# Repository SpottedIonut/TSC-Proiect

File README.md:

#### Spirchez Mihai 331CA
## Block Diagram
```mermaid
graph TD
  %% Center
  ESP[<span style='color:#e0ccff'><b>ESP32</b></span>]

  %% SPI Devices (Top)
  NOR[<span style='color:#ffcccc'>External NOR Flash</span>]
  EPD[<span style='color:#ffcccc'>E-Paper Display</span>]
  SD[<span style='color:#ffcccc'>SD Card</span>]

  NOR -->|SPI| ESP
  ESP -->|SPI| EPD
  SD -->|SPI| ESP

  %% I2C Devices (Bottom)
  RTC[<span style='color:#cce5ff'>RTC Module</span>]
  ENV[<span style='color:#cce5ff'>Environmental Sensor</span>]
  BCL[<span style='color:#cce5ff'>Battery Charge Level</span>]

  RTC -->|I2C| ESP
  ENV -->|I2C| ESP
  BCL -->|I2C| ESP

  %% Buttons (Left)
  BTN[<span style='color:#d4f4dd'>Buttons</span>]
  BTN --> ESP

  %% USB and Power (Right)
  USB[USB C Connector]
  CHG[Charging Controller]
  REG[Voltage Regulator]
  BATT[Battery]

  ESP -->|USB| USB
  USB --> CHG
  USB --> REG
  BATT --> CHG
  BATT --> REG

```
## Bill of Materials
|Component|Description|Purchase|Datasheet|
|---------|-----------|--------|---------|
|EAGLE-LTSPICE_CC0402 | Capacitor | https://eu.mouser.com/ProductDetail/KEMET/C0402C475K8PACTU?qs=ulEaXIWI0c9ebKRT3r3htg%3D%3D | https://eu.mouser.com/datasheet/2/447/KEM_C1006_X5R_SMD-3316465.pdf
|ESP32_WROVER_EAGLE-LTSPICE_RR0402 | Resistor | https://eu.mouser.com/ProductDetail/Vishay-Beyschlag/MCS04020D9101BE000?qs=sGAEpiMZZMvdGkrng054twKDKoBh%252BscnK%2FuqkNk9X%252BqO%2Fz5%2F0u93Ow%3D%3D  | https://www.vishay.com/docs/28700/mcx0x0xpre.pdf
|RCL_CPOL-EUCT3528 | Capacitor | https://eu.mouser.com/ProductDetail/Nichicon/LGN2W101MELA25?qs=Fe64Qgzkstf1zMszMsgRoA%3D%3D | https://eu.mouser.com/datasheet/2/293/e_lgn-3082370.pdf
|ADAFRUIT_LEDCHIP-LED0603 | LED | https://eu.mouser.com/ProductDetail/ams-OSRAM/KG-EELP41.22-PHRH-35-A8J8-20-R18?qs=ZcfC38r4Posajg8ZvCDQkg%3D%3D | https://eu.mouser.com/datasheet/2/588/KG_EELP41_22_EN-3572852.pdf
|CPH3225A | Capacitor | https://eu.mouser.com/ProductDetail/Seiko-Semiconductors/CPH3225A?qs=3etwrb1wR%252BhUOph6lAO7eg%3D%3D | https://eu.mouser.com/datasheet/2/360/Seiko_Instruments_MicroBattery_E_20230330_2024Jan_-3561061.pdf
|ESP32_WROVER_SPARKFUN-DISCRETESEMI_MOSFET_PCH-DMG2305UX-7 | Transistor | https://eu.mouser.com/ProductDetail/Diodes-Incorporated/DMG2305UX-7?qs=L1DZKBg7t5F%2FNBHrjfxC%252Bg%3D%3D | https://www.diodes.com/assets/Datasheets/DMG2305UX.pdf
|ESP32_WROVER_AVX---SD0805S020S1R0_AVX_SD0805S020S1R0_0_0AVX_SD0805S020S1R0_0_0 | Diode | https://eu.mouser.com/ProductDetail/ROHM-Semiconductor/SCS310AMC7G?qs=iLKYxzqNS75xiccEgNnX2g%3D%3D | https://fscdn.rohm.com/en/products/databook/datasheet/discrete/sic/sbd/scs310am-e.pdf
|SI1308EDL-T1-GE3 | Transistor | https://eu.mouser.com/ProductDetail/Vishay-Semiconductors/SI1308EDL-T1-GE3?qs=bX1%252BNvsK%2FBramh9tgpOaEw%3D%3D | https://www.vishay.com/docs/63399/si1308edl.pdf
|ESP32C6_VARISTORCN1812 | Varistor | https://eu.mouser.com/ProductDetail/Schurter/PFMF.050.2?qs=1auRipcfynCums5v1iucSA%3D%3D | https://eu.mouser.com/datasheet/2/358/typ_PFMF-1275918.pdf
|ESP32_WROVER_BME680_BME680 | Integrated Environmental Unit | https://eu.mouser.com/ProductDetail/M5Stack/U001-C?qs=e8oIoAS2J1R2mB7ZY1%252BSZg%3D%3D | https://docs.m5stack.com/en/unit/envIII
|ESP32-C6-WROOM-1-N8 | MicroController | https://eu.mouser.com/ProductDetail/Espressif-Systems/ESP32-C6?qs=Imq1NPwxi75noDtUpuVuWw%3D%3D | https://eu.mouser.com/datasheet/2/891/esp32_c6_datasheet_en-3304070.pdf
| 744043680IND_4828-WE-TPC_WRE | Inductor | https://eu.mouser.com/ProductDetail/Wurth-Elektronik/744043680?qs=PGXP4M47uW6VkZq%252BkzjrHA%3D%3D | https://www.we-online.com/components/products/datasheet/744043680.pdf
|SI1308EDL-T1-GE3 | Transistor | https://eu.mouser.com/ProductDetail/Vishay-Semiconductors/SI1308EDL-T1-GE3?qs=bX1%252BNvsK%2FBramh9tgpOaEw%3D%3D | https://www.vishay.com/docs/63399/si1308edl.pdf
| BD5229G-TR | Voltage Detector | https://eu.mouser.com/ProductDetail/ROHM-Semiconductor/BD5229G-TR?qs=sGAEpiMZZMutXGli8Ay4kAMqIQqqdOUlDFcDfPDPIK4%3D | https://fscdn.rohm.com/en/products/databook/datasheet/ic/power/voltage_detector/bd52xxg-e.pdf
|DS3231SN# | RTC Module | https://eu.mouser.com/ProductDetail/Analog-Devices-Maxim-Integrated/DS3231SN?qs=1eQvB6Dk1vhUlr8%2FOrV0Fw%3D%3D | https://eu.mouser.com/datasheet/2/609/DS3231-3421123.pdf
|USBLC6-2SC6Y | ESD Protection | https://eu.mouser.com/ProductDetail/STMicroelectronics/USBLC6-2SC6Y?qs=gNDSiZmRJS%2FOgDexvXkdow%3D%3D | https://eu.mouser.com/datasheet/2/389/usblc6_2sc6y-1852505.pdf
|W25Q512JVEIQ | Flash Memory | https://eu.mouser.com/ProductDetail/Winbond/W25Q512JVEIQ?qs=l7cgNqFNU1jw6svr3at6tA%3D%3D | https://eu.mouser.com/datasheet/2/949/Winbond_W25Q512JV_Datasheet-3240039.pdf
|SAMACSYS_PARTS_USB4110-GF-A | USB Connector | https://eu.mouser.com/ProductDetail/GCT/USB4110-GF-A?qs=KUoIvG%2F9IlYiZvIXQjyJeA%3D%3D | https://eu.mouser.com/datasheet/2/837/GCT_USB4110_Product_Drawing___20k_cycles-3455479.pdf
|FH34SRJ | E-Paper Display Header | https://eu.mouser.com/ProductDetail/Hirose-Connector/FH34SRJ-7S-0.5SH50?qs=vcbW%252B4%252BSTIqHa4IamMh36g%3D%3D | https://eu.mouser.com/datasheet/2/185/FH34SRJ_7S_0_5SH_50__CL0580_1200_0_50_2DDrawing_00-1615127.pdf
|MAX17048G+T10 | Battery Management | https://eu.mouser.com/ProductDetail/Analog-Devices-Maxim-Integrated/MAX17048G%2bT10?qs=D7PJwyCwLAoGnnn8jEPRBQ%3D%3D | https://eu.mouser.com/datasheet/2/609/MAX17048_MAX17049-3469099.pdf
|MCP73831 | Battery Controller | https://eu.mouser.com/ProductDetail/Microchip-Technology/MCP73831T-2ATI-MC?qs=yUQqVecv4qs9k7ug0bEXiw%3D%3D | https://eu.mouser.com/datasheet/2/268/MCP73831_Family_Data_Sheet_DS20001984H-3441711.pdf
|112A-TAAR-R03_ATTEND | SD Card Mount | https://store.comet.srl.ro/Catalogue/Product/43497/ | https://store.comet.srl.ro/Catalogue/Product/43497/
|XC6220A331MR-G | LDO Voltage Regulator | https://eu.mouser.com/ProductDetail/Torex-Semiconductor/XC6220A331MR-G?qs=AsjdqWjXhJ8ZSWznL1J0gg%3D%3D | https://eu.mouser.com/datasheet/2/760/xc6220-3371556.pdf

## Hardware components
- ESP32-C6-WROOM-1-N8 Microcontroller

### Communication interfaces

| Communication interface | Connected Components |
|--------------|----------------------|
| I2C        | RTC, BME688, Battery Level     |
| SPI        | SD Card, E-Paper Display, NOR Flash     |
| USB        | USB C Connector / Power     |

### ESP32-C6-WROOM-1-N8 Pin Mapping

| ESP32 Pin | Signal | Purpose |
|--------------|----------------------|---------|
| IO0        | INT_RTC     | RTC communication |
| IO1        | 32KHZ     | RTC communication |
| IO2        | MISO     | SD Card, NOR Flash |
| IO3        | EPD_BUSY     | EPD status |
| IO4        | SS_SD | SD Card |
| IO5        | EPD_DC | EPD Data/Command |
| IO6        | SCK  | BME688, SD Card, NOR Flash |
| IO7        | MOSI   | SD Card, NOR Flash, EPD |
| IO8        | GPIO8 | SD card select |
| IO9        | IO/BOOT   | Boot button |
| IO10       | EPD_CS   | EPD chip select|
| IO11       | FLASH_CS    | NOR Flash chip select |
| IO12       | USB_D-| USB communication |
| IO13       | USB_D+        | USB communication |
| IO15       | IO/CHANGE   | Button change |
| IO16       | TX   | Transmit |
| IO17       | RX   | Receive |
| IO18       | RTC_RST   | RTC reset |
| IO19       | I2C_PW   | BME688 power management |
| IO20       | EPD_3V3_C   | EPD |
| IO21       | SDA   | RTC, BME688, Battery Level (I2C data) |
| IO22       | SCL   | RTC, BME688, Battery Level (I2C clock) |
| IO23       | EPD_RST   | EPD reset |

- Real-Time Clock Module (RTC)
  - A DS3231SN RTC module
  - It communicates through I2C with the microcontroller
  - Pin connections:
      - SCL -> IO22
      - SDA -> IO21
      - RTC_RST -> IO18
      - 32KHZ -> IO1
      - INT_RTC -> IO0
- SD Card
  - It communicates through SPI
  - Pin connections:
    - MISO - IO2
    - SCK - IO6
    - MOSI - IO7
    - SS_SD - IO4
- E-Paper Display (EPD)
  - It communicates through SPI
  - Pin connections:
    - EPD_CS -> IO10
    - EPD_DC -> IO5
    - EPD_RST -> IO23
    - EPD_BUSY -> IO3
    - MOSI, SCK -> shared with SD
- Environmental Sensor
  - BME688 sensor
  - It communicates through I2C
  - Pin connections:
      - SCL -> IO22
      - SDA -> IO21
- Li-Po Battery Charging Controller
  - Battery Charge Level
    - It communicates through I2C
    - Pin connections:
        - SCL -> IO22
        - SDA -> IO21
- LDO Voltage Regulator
  - Lowers the 5V to 3.3V for the microcontroller and the attached modules
- SPI ESD Protection Lines
- NOR Flash 64MB
  - It communicates through SPI
  - Pin connections:
    - FLASH_CS -> IO11
    - SCK, MOSI, MISO
- USB
  - USB_D- -> IO12
  - USB_D+ -> IO13
- Buttons for user input
  - RESET -> EN
  - IO/BOOT -> IO9
  - IO/CHANGE -> IO15
- Qwiic / Stemma QT Connector
  - It communicates through I2C
  - SCL, SDA

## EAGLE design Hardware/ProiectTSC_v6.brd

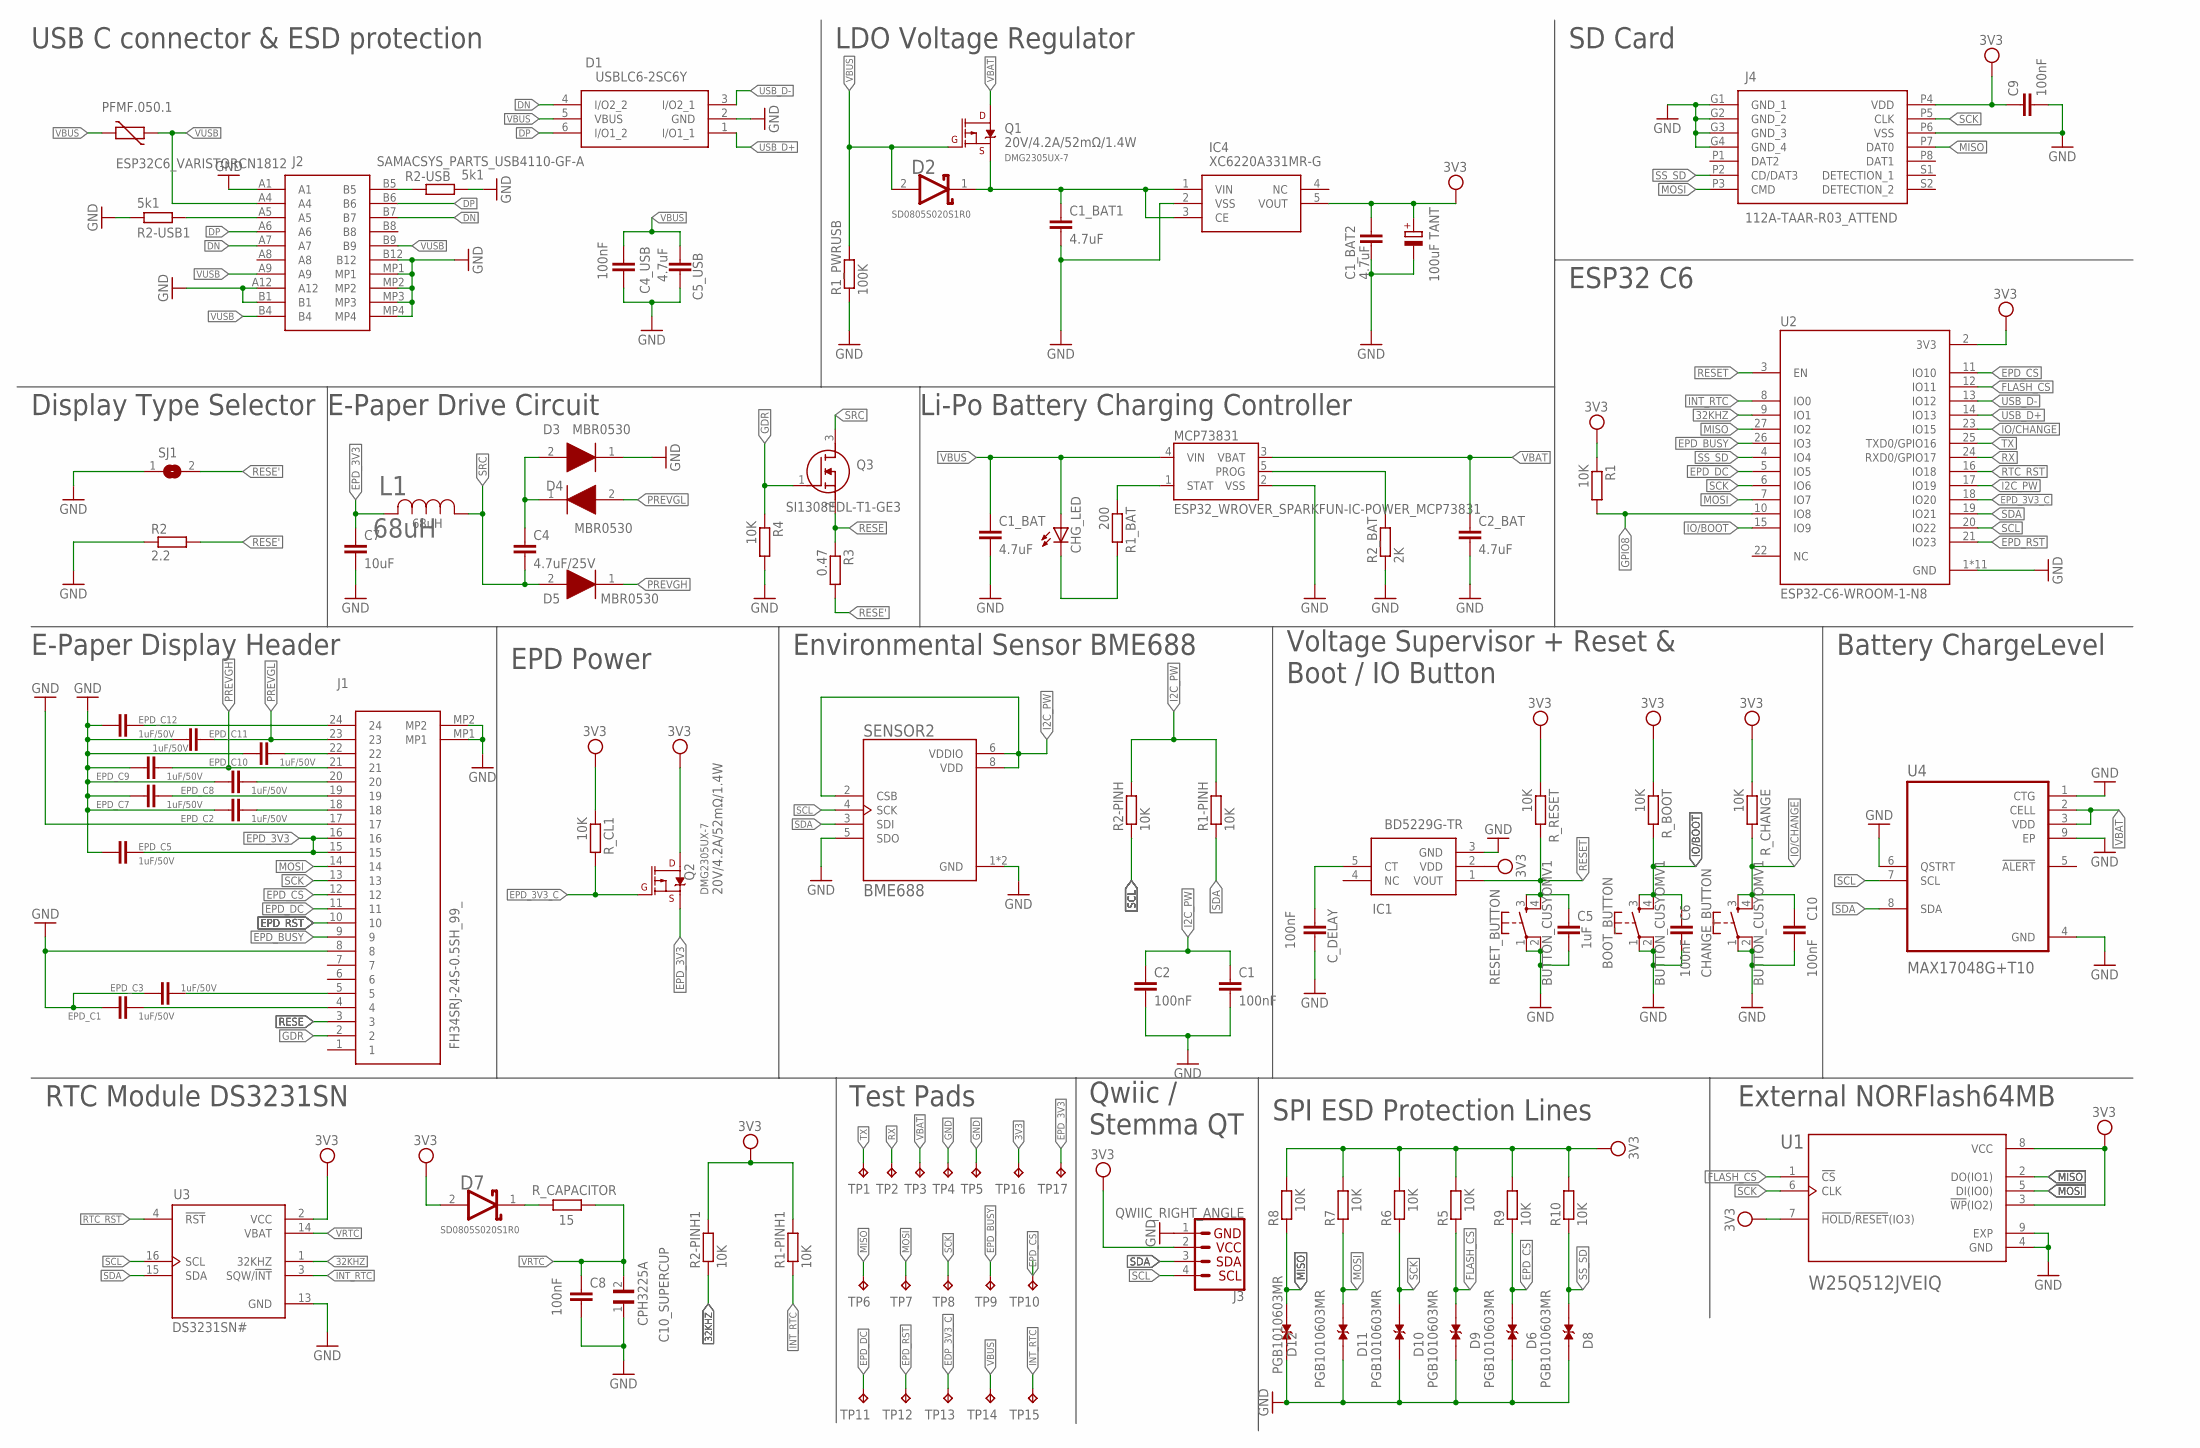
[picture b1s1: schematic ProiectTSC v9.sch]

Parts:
BOOT_BUTTON: BUTTON_CUSYOMV1; MYBUTTON
C1, C2, C4_USB, C6, C8, C9, C10: 100nF; EAGLE-LTSPICE_C0402
C1_BAT, C1_BAT1, C1_BAT2, C2_BAT, C5_USB: 4.7uF; EAGLE-LTSPICE_C0402
C4: 4.7uF/25V; EAGLE-LTSPICE_C0402
C5: 1uF; EAGLE-LTSPICE_C0402
C7: 10uF; EAGLE-LTSPICE_C0402
C10_SUPERCUP: CPH3225A; CAPCP3225X100N
CHANGE_BUTTON: BUTTON_CUSYOMV1; MYBUTTON
CHG_LED: ADAFRUIT_LEDCHIP-LED0603; ADAFRUIT_CHIP-LED0603
C_DELAY: 100nF; EAGLE-LTSPICE_C0402
D1: USBLC6-2SC6Y; SOT95P280X145-6N
D2, D7: SD0805S020S1R0; ESP32_WROVER_AVX---SD0805S020S1R0_AVX_SD0805S020S1R0_0
D3, D4, D5: MBR0530; SOD3716X135N
D6, D8, D9, D10, D11, D12: PGB1010603MR; DIOC1608X36N
EPD_C1, EPD_C2, EPD_C3, EPD_C5, EPD_C7, EPD_C8, EPD_C9, EPD_C10, EPD_C11, EPD_C12: 1uF/50V; EAGLE-LTSPICE_C0402
IC1: BD5229G-TR; SOT95P280X125-5N
IC4: XC6220A331MR-G; SOT95P280X120-5N
J1: FH34SRJ-24S-0.5SH_99_; FH34SRJ24S05SH99
J2: SAMACSYS_PARTS_USB4110-GF-A; SAMACSYS_PARTS_USB4110GFA
J3: QWIIC_RIGHT_ANGLE; JST04_1MM_RA
J4: 112A-TAAR-R03_ATTEND; 112ATAARR03ATTEND
L1: 68uH; IND_4828-WE-TPC_WRE
MCP73831: ESP32_WROVER_SPARKFUN-IC-POWER_MCP73831; ESP32_WROVER_SPARKFUN-IC-POWER_SOT23-5
PFMF.050.1: ESP32C6_VARISTORCN1812; ESP32C6_VARISTOR_CT/CN1812
Q1, Q2: 20V/4.2A/52mΩ/1.4W; ESP32_WROVER_SPARKFUN-DISCRETESEMI_SOT23-3
Q3: SI1308EDL-T1-GE3; SOT65P210X110-3N
R1, R1-PINH, R1-PINH1, R2-PINH, R2-PINH1, R4, R5, R6, R7, R8, R9, R10: 10K; ESP32_WROVER_EAGLE-LTSPICE_R0402
R1_BAT: 200; ESP32_WROVER_EAGLE-LTSPICE_R0402
R1_PWRUSB: 100K; ESP32_WROVER_EAGLE-LTSPICE_R0402
R2: 2.2; ESP32_WROVER_EAGLE-LTSPICE_R0402
R2-USB, R2-USB1: 5k1; ESP32_WROVER_EAGLE-LTSPICE_R0402
R2_BAT: 2K; ESP32_WROVER_EAGLE-LTSPICE_R0402
R3: 0.47; ESP32_WROVER_EAGLE-LTSPICE_R0402
RESET_BUTTON: BUTTON_CUSYOMV1; MYBUTTON
R_BOOT: 10K; ESP32_WROVER_EAGLE-LTSPICE_R0402
R_CAPACITOR: 15; ESP32_WROVER_EAGLE-LTSPICE_R0402
R_CHANGE: 10K; ESP32_WROVER_EAGLE-LTSPICE_R0402
R_CL1: 10K; ESP32_WROVER_EAGLE-LTSPICE_R0402
R_RESET: 10K; ESP32_WROVER_EAGLE-LTSPICE_R0402
SENSOR2: BME688; ESP32_WROVER_BME680_PSON80P300X300X100-8N
SJ1: SJ
TANT: 100uF; RCL_CT3528
TP1, TP2, TP3, TP4, TP5, TP6, TP7, TP8, TP9, TP10, TP11, TP12, TP13, TP14, TP15, TP16, TP17: TPTP20R; TP20R
U1: W25Q512JVEIQ; SON127P600X800X80-9N
U2: ESP32-C6-WROOM-1-N8; XCVR_ESP32-C6-WROOM-1-N8
U3: DS3231SN#; SOIC127P1032X265-16N
U4: MAX17048G+T10; SON50P200X200X80-9N

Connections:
3V3: C1_BAT2.1, C9.1, D7.2 (ANODE), IC1.2 (VDD), IC4.5 (VOUT), J3.2, J4.P4 (VDD), Q2.3 (D), R1.1, R1-PINH1.2, R2-PINH1.2, R5.2, R6.2, R7.2, R8.2, R9.2, R10.2, R_BOOT.1, R_CHANGE.1, R_CL1.1, R_RESET.1, TANT.+, TP16.TP, U1.3 (!WP!(IO2)), U1.7 (!HOLD!/!RESET!(IO3)), U1.8 (VCC), U2.2 (3V3), U3.2 (VCC)
32KHZ: R2-PINH1.1, U2.9 (IO1), U3.1 (32KHZ)
DN: D1.4 (I/O2_2), J2.A7, J2.B7
DP: D1.6 (I/O1_2), J2.A6, J2.B6
EDP_3V3_C: TP13.TP
EPD_3V3: C7.1, EPD_C5.1, J1.15, J1.16, L1.2, Q2.2 (S), TP17.TP
EPD_3V3_C: Q2.1 (G), R_CL1.2, U2.18 (IO20)
EPD_BUSY: J1.9, TP9.TP, U2.26 (IO3)
EPD_CS: D6.1, J1.12, R9.1, TP10.TP, U2.11 (IO10)
EPD_DC: J1.11, TP11.TP, U2.5 (IO5)
EPD_RST: J1.10, TP12.TP, U2.21 (IO23)
FLASH_CS: D9.1, R5.1, U1.1 (!CS), U2.12 (IO11)
GDR: J1.2, Q3.1 (G), R4.1
GND: BOOT_BUTTON.1, BOOT_BUTTON.2, C1.2, C1_BAT.2, C1_BAT1.2, C1_BAT2.2, C2.2, C2_BAT.2, C4_USB.2, C5.2, C5_USB.2, C6.2, C7.2, C8.2, C9.2, C10.2, C10_SUPERCUP.1, CHANGE_BUTTON.1, CHANGE_BUTTON.2, C_DELAY.2, D1.2 (GND), D3.1 (K), D6.2, D8.2, D9.2, D10.2, D11.2, D12.2, EPD_C1.2, EPD_C2.2, EPD_C3.2, EPD_C5.2, EPD_C7.2, EPD_C8.2, EPD_C9.2, EPD_C10.2, EPD_C11.2, EPD_C12.2, IC1.3 (GND), IC4.2 (VSS), J1.8, J1.17, J1.MP1, J1.MP2, J2.A1, J2.A12, J2.B1, J2.B12, J2.MP1, J2.MP2, J2.MP3, J2.MP4, J3.1, J4.G1 (GND_1), J4.G2 (GND_2), J4.G3 (GND_3), J4.G4 (GND_4), J4.P6 (VSS), MCP73831.2 (VSS), R1_PWRUSB.1, R2.1, R2-USB.2, R2-USB1.1, R2_BAT.1, R4.2, RESET_BUTTON.1, RESET_BUTTON.2, SENSOR2.1 (GND), SENSOR2.5 (SDO), SENSOR2.7 (GND), SJ1.1, TANT.-, TP4.TP, TP5.TP, U1.4 (GND), U1.9 (EXP), U2.1 (GND), U2.28 (GND), U2.29_1 (GND), U2.29_2 (GND), U2.29_3 (GND), U2.29_4 (GND), U2.29_5 (GND), U2.29_6 (GND), U2.29_7 (GND), U2.29_8 (GND), U2.29_9 (GND), U3.13 (GND), U4.1 (CTG), U4.4 (GND), U4.6 (QSTRT), U4.9 (EP)
GPIO8: R1.2, U2.10 (IO8)
I2C_PW: C1.1, C2.1, R1-PINH.2, R2-PINH.2, SENSOR2.2 (CSB), SENSOR2.6 (VDDIO), SENSOR2.8 (VDD), U2.17 (IO19)
INT_RTC: R1-PINH1.1, TP15.TP, U2.8 (IO0), U3.3 (SQW/!INT)
IO/BOOT: BOOT_BUTTON.3, BOOT_BUTTON.4, C6.1, R_BOOT.2, U2.15 (IO9)
IO/CHANGE: C10.1, CHANGE_BUTTON.3, CHANGE_BUTTON.4, R_CHANGE.2, U2.23 (IO15)
MISO: D12.1, J4.P7 (DAT0), R8.1, TP6.TP, U1.2 (DO(IO1)), U2.27 (IO2)
MOSI: D11.1, J1.14, J4.P3 (CMD), R7.1, TP7.TP, U1.5 (DI(IO0)), U2.7 (IO7)
unnamed: MCP73831.5 (PROG), R2_BAT.2
unnamed: J2.A5, R2-USB1.2
unnamed: MCP73831.1 (STAT), R1_BAT.1
unnamed: C4.1, D3.2 (A), D4.1 (K)
unnamed: C1_BAT1.1, D2.1 (CATHODE), IC4.1 (VIN), IC4.3 (CE), Q1.2 (S)
unnamed: CHG_LED.C, R1_BAT.2
unnamed: EPD_C12.1, J1.24
unnamed: J2.B5, R2-USB.1
unnamed: EPD_C10.1, J1.22
unnamed: C_DELAY.1, IC1.5 (CT)
unnamed: D7.1 (CATHODE), R_CAPACITOR.2
unnamed: EPD_C8.1, J1.20
unnamed: EPD_C7.1, J1.19
unnamed: EPD_C2.1, J1.18
unnamed: EPD_C1.1, J1.4
unnamed: EPD_C3.1, J1.5
PREVGH: D5.1 (K), EPD_C9.1, J1.21
PREVGL: D4.2 (A), EPD_C11.1, J1.23
RESE: J1.3, Q3.2 (S), R3.1
RESE': R2.2, R3.2, SJ1.2
RESET: C5.1, IC1.1 (VOUT), RESET_BUTTON.3, RESET_BUTTON.4, R_RESET.2, U2.3 (EN)
RTC_RST: U2.16 (IO18), U3.4 (!RST)
RX: TP2.TP, U2.24 (RXD0/GPIO17)
SCK: D10.1, J1.13, J4.P5 (CLK), R6.1, TP8.TP, U1.6 (CLK), U2.6 (IO6)
SCL: J3.4, R2-PINH.1, SENSOR2.4 (SCK), U2.20 (IO22), U3.16 (SCL), U4.7 (SCL)
SDA: J3.3, R1-PINH.1, SENSOR2.3 (SDI), U2.19 (IO21), U3.15 (SDA), U4.8 (SDA)
SRC: C4.2, D5.2 (A), L1.1, Q3.3 (D)
SS_SD: D8.1, J4.P2 (CD/DAT3), R10.1, U2.4 (IO4)
TX: TP1.TP, U2.25 (TXD0/GPIO16)
USB_D+: D1.1 (I/O1_1), U2.14 (IO13)
USB_D-: D1.3 (I/O2_1), U2.13 (IO12)
VBAT: C2_BAT.1, MCP73831.3 (VBAT), Q1.3 (D), TP3.TP, U4.2 (CELL), U4.3 (VDD)
VBUS: C1_BAT.1, C4_USB.1, C5_USB.1, CHG_LED.A, D1.5 (VBUS), D2.2 (ANODE), MCP73831.4 (VIN), PFMF.050.1.2, Q1.1 (G), R1_PWRUSB.2, TP14.TP
VRTC: C8.1, C10_SUPERCUP.2, R_CAPACITOR.1, U3.14 (VBAT)
VUSB: J2.A4, J2.A9, J2.B4, J2.B9, PFMF.050.1.1

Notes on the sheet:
USB C connector & ESD protection
LDO Voltage Regulator
SD Card
ESP32 C6
Display Type Selector
E-Paper Drive Circuit
Li-Po Battery Charging Controller
E-Paper Display Header
EPD Power
Environmental Sensor BME688
Voltage Supervisor + Reset & Boot / IO Button
Battery ChargeLevel
External NORFlash64MB
SPI ESD Protection Lines
Qwiic / Stemma QT
Test Pads
RTC Module DS3231SN

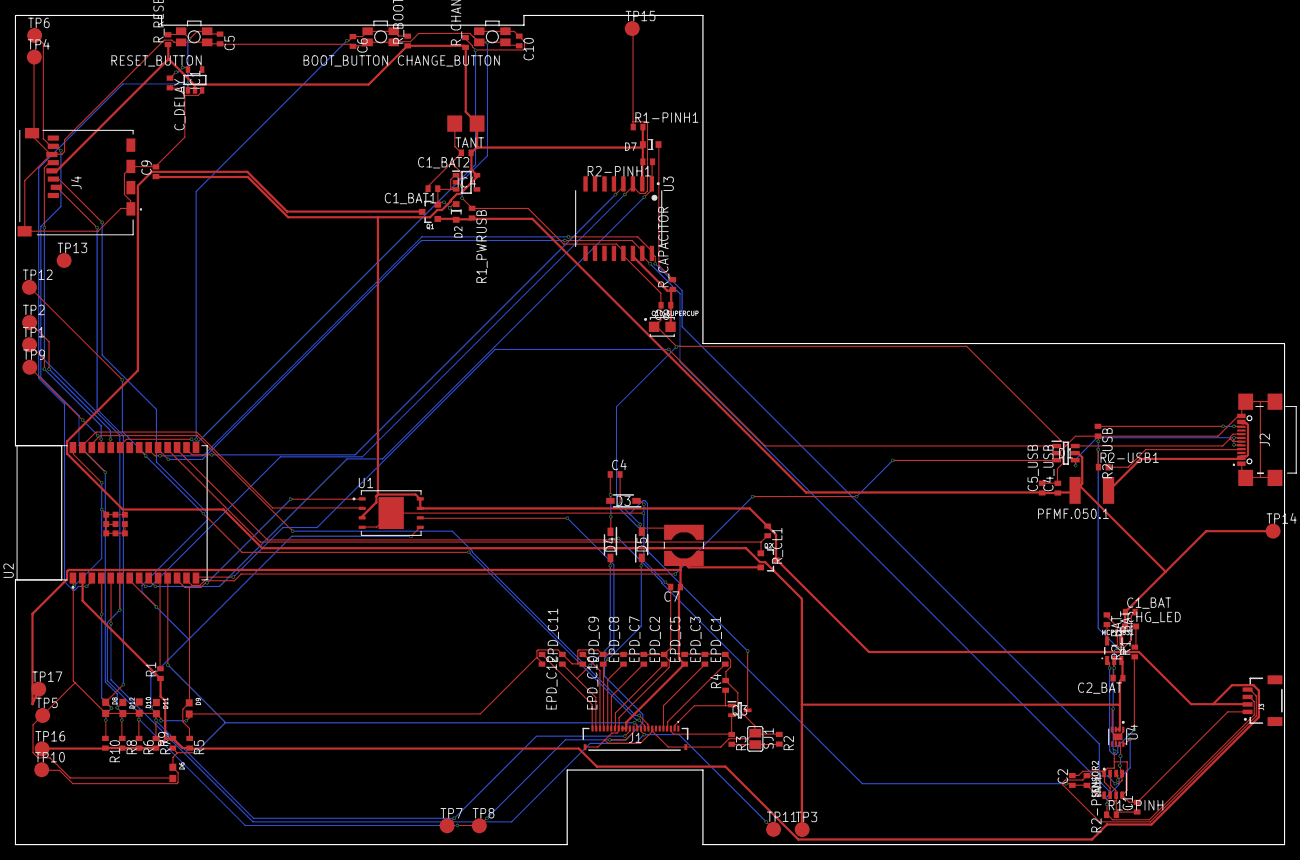
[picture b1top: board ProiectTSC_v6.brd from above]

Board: 2 copper layers, 170.2 x 111.2 mm, 103 parts (0 on the bottom side), 55 nets.

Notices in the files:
parts and their libraries:
DeskAssistant v19 v1: COPYRIGHT: Copyright (C) 2024 Ultra Librarian. All rights reserved.
